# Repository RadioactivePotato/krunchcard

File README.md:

# krunchcard
A card-sized NFC business card

# About
This is a simple credit card sized business card with NFC

# Images

<details>
<summary>Schematic (click to expand)</summary>

| Schematic |
|-----------|
|  |

</details>

| PCB | 3D Preview |
|-----|------------|
|  |  |
|  |  |

# BOM
| Qty | Item                               | Notes                             | Cost (USD) | URL                                                                                  |
|-----|------------------------------------|-----------------------------------|------------|--------------------------------------------------------------------------------------|
| 5   | 1206 220nF SMD Capacitor           | C107186                        | 0.50       | [LCSC](https://lcsc.com/product-detail/Multilayer-Ceramic-Capacitors-MLCC-SMD-SMT_YAGEO-CC1206KKX7R9BB224_C107186.html)                 |
| 5   | 1206 Green SMD LED                 | C965825                        | 0.44       | [LCSC](https://lcsc.com/product-detail/LED-Indication-Discrete_XINGLIGHT-XL-3216UGC_C965825.html)                 |
| 5   | 1206 47Ω SMD Resistor              | C140015                        | 0.21       | [LCSC](https://lcsc.com/product-detail/Chip-Resistor-Surface-Mount_FH-RS-06K470JT_C140015.html)                 |
| 5   | NXP NT3H2111W0FTTJ IC              | C2654884                       | 0.70       | [LCSC](https://lcsc.com/product-detail/RFID-ICs_NXP-NT3H2111W0FTTJ_C2654884.html)                 |
| 5   | PCB                                | JLCPCB                         | 3.51       | [JLCPCB](https://JLCPCB.com)                 |
| 1   | Solder Paste                       | Manual soldering               | 8.57       | [Amazon](https://www.amazon.co.uk/gp/product/B0D4QTT6S3)                 |
| 1   | LCSC Shipping Cost + Fees          | 5.58(Shipping) + 3(Handling)   | 8.58       | - |
| - | - | - | 22.51 | - |

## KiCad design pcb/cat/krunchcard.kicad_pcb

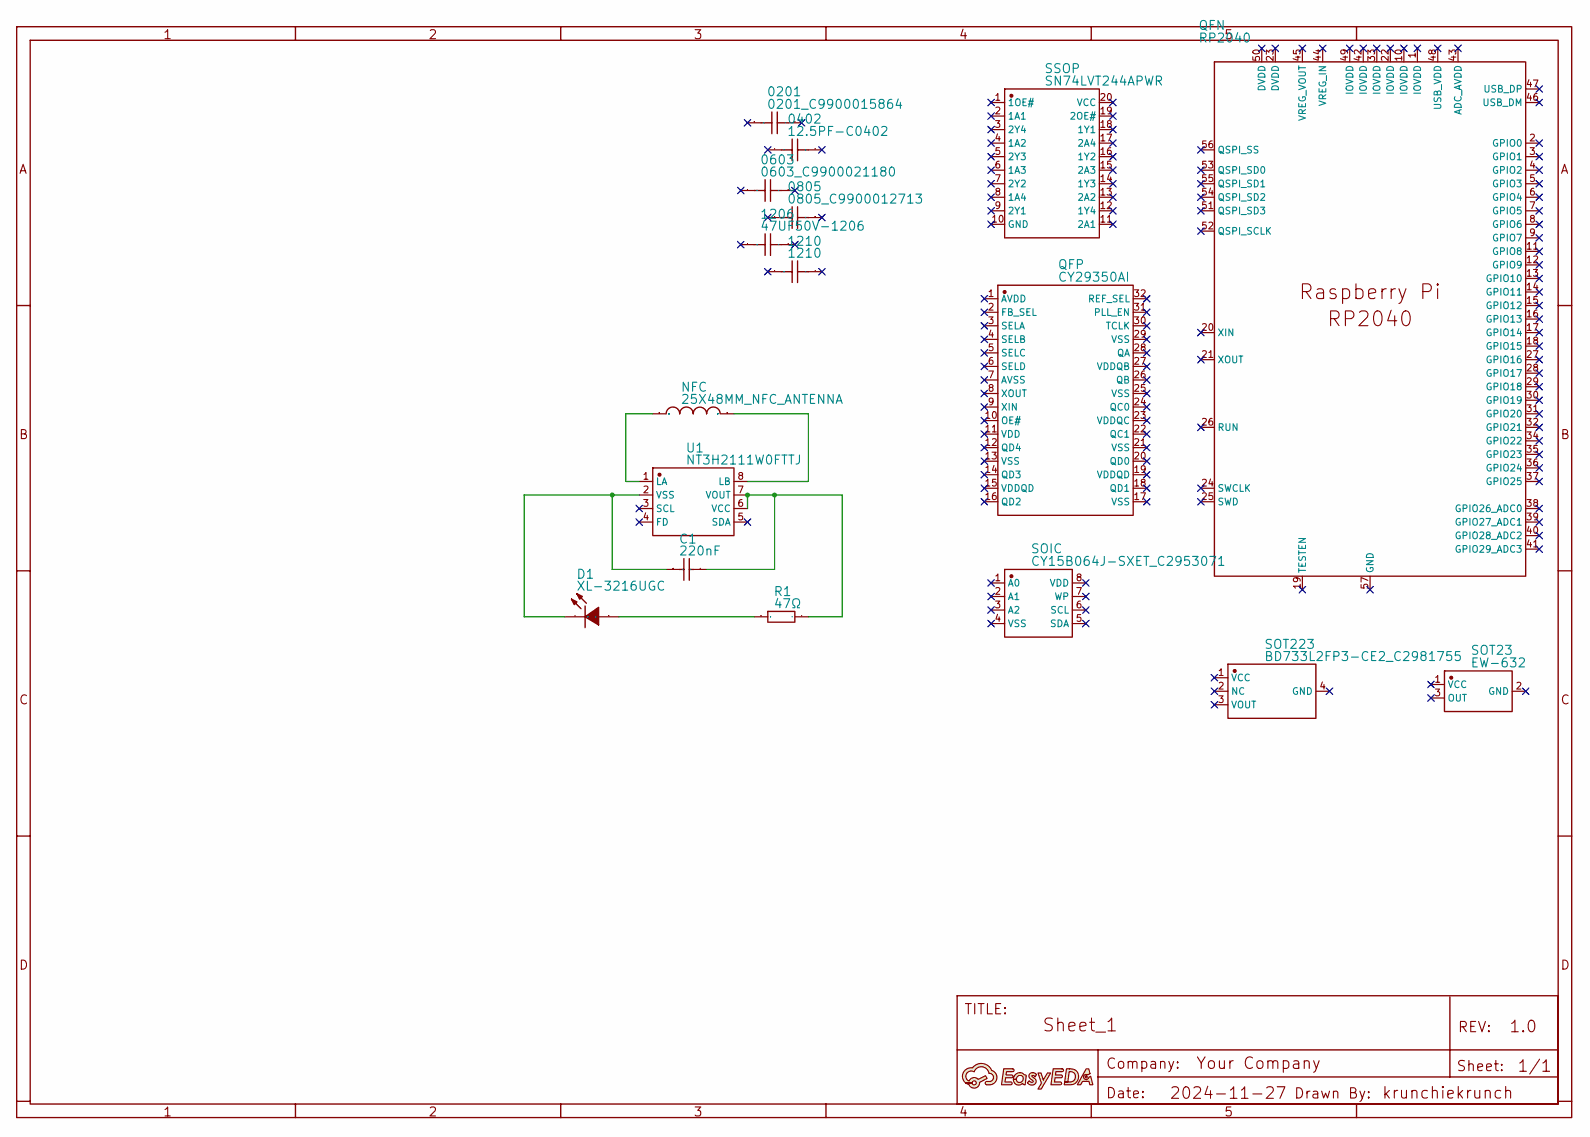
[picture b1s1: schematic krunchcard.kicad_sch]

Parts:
0201: 0201_C9900015864; Manufacturer Part 0201
0402: 12.5PF-C0402; Manufacturer Part 12.5pF-C0402
0603: 0603_C9900021180; Manufacturer Part 0603
0805: 0805_C9900012713; Manufacturer Part 0805
1206: 47UF50V-1206; Manufacturer Part 47uF50V-1206
1210: 1210; Manufacturer Part 1210
A: A; Manufacturer Part ?
C1: 220nF; Manufacturer Part CC1206KKX7R9BB224
D1: XL-3216UGC; Manufacturer Part XL-3216UGC
NFC: 25X48MM_NFC_ANTENNA
QFN: RP2040; Manufacturer Part RP2040
QFP: CY29350AI; Manufacturer Part CY29350AI
R1: 47Ω; Manufacturer Part RS-06K470JT
SOIC: CY15B064J-SXET_C2953071; Manufacturer Part CY15B064J-SXET
SOT23: EW-632; Manufacturer Part EW-632
SOT223: BD733L2FP3-CE2_C2981755; Manufacturer Part BD733L2FP3-CE2
SSOP: SN74LVT244APWR; Manufacturer Part SN74LVT244APWR
U1: NT3H2111W0FTTJ; Manufacturer Part NT3H2111W0FTTJ

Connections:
NFC_P$1: NFC.P$1, U1.1 (LA)
NFC_P$2: NFC.P$2, U1.8 (LB)
R1_1: D1.1 (A), R1.1
U1_2: C1.1, D1.2 (K), U1.2 (VSS)
U1_6: C1.2, R1.2, U1.6 (VCC), U1.7 (VOUT)

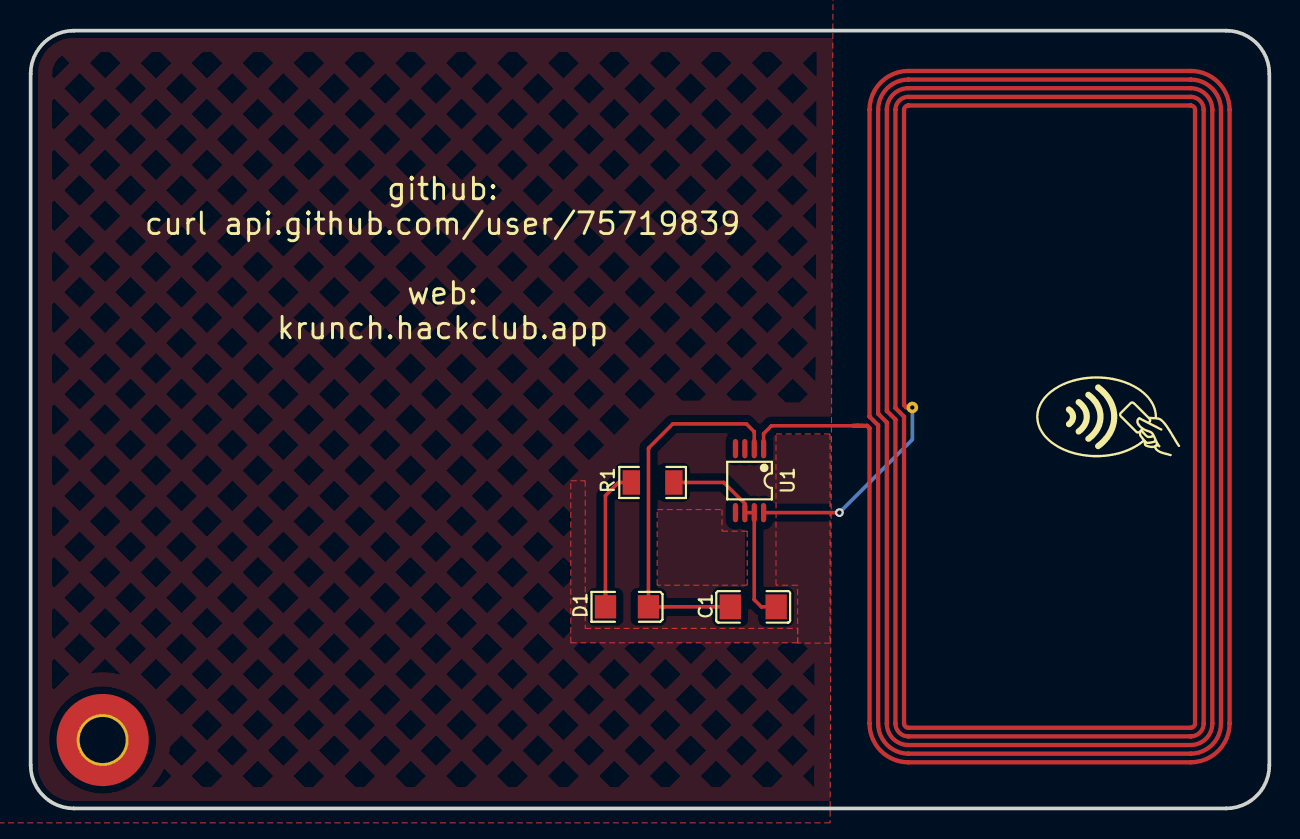
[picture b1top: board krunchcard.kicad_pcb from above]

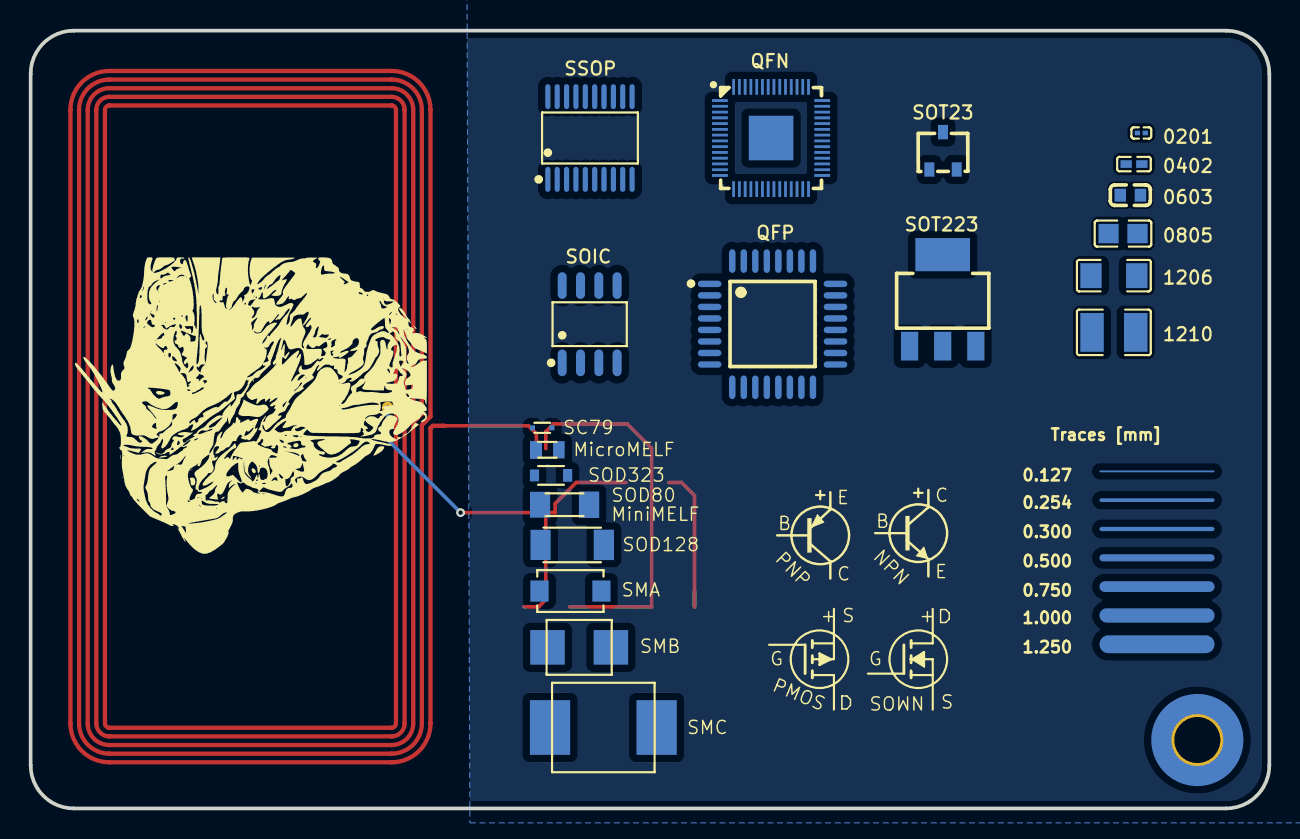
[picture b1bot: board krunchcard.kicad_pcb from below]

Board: 2 copper layers, 86.0 x 54.0 mm, 36 parts (24 on the bottom side), 5 nets.

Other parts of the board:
E$41: MICROMELF-R
E$42: SC79_INFINEON
E$43: SMA-DIODE
E$44: SMB-DIODE
E$45: SMC
E$47: SOD-128
E$48: SOD-323
E$49: SOD80C
E$50: NMOS-SYMB
E$51: PMOS-SYMB
E$54: NPN-SYMB
E$59: PNP-SYMB
Pad_gge145080: Pad_gge145080
Pad_gge145083: Pad_gge145083
Pad_gge145086: Pad_gge145086
Pad_gge145089: Pad_gge145089
Pad_gge145092: Pad_gge145092
Pad_gge145095: Pad_gge145095
Pad_gge145098: Pad_gge145098

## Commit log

2025-07-18 repo setup
2025-07-18 july 18
2025-07-19 july 19
2025-07-19 images
2025-07-19 pcb files
2025-07-19 updated pcb (see july 20 journal)
2025-07-19 july 20
2025-07-20 updated back of pcb
2025-07-20 fixed file name
2025-07-20 fixed filename
2025-07-20 prod files
2025-07-20 gerber update
2025-07-20 updated copper pour around antenna, reworked infos
2025-07-28 cat added
